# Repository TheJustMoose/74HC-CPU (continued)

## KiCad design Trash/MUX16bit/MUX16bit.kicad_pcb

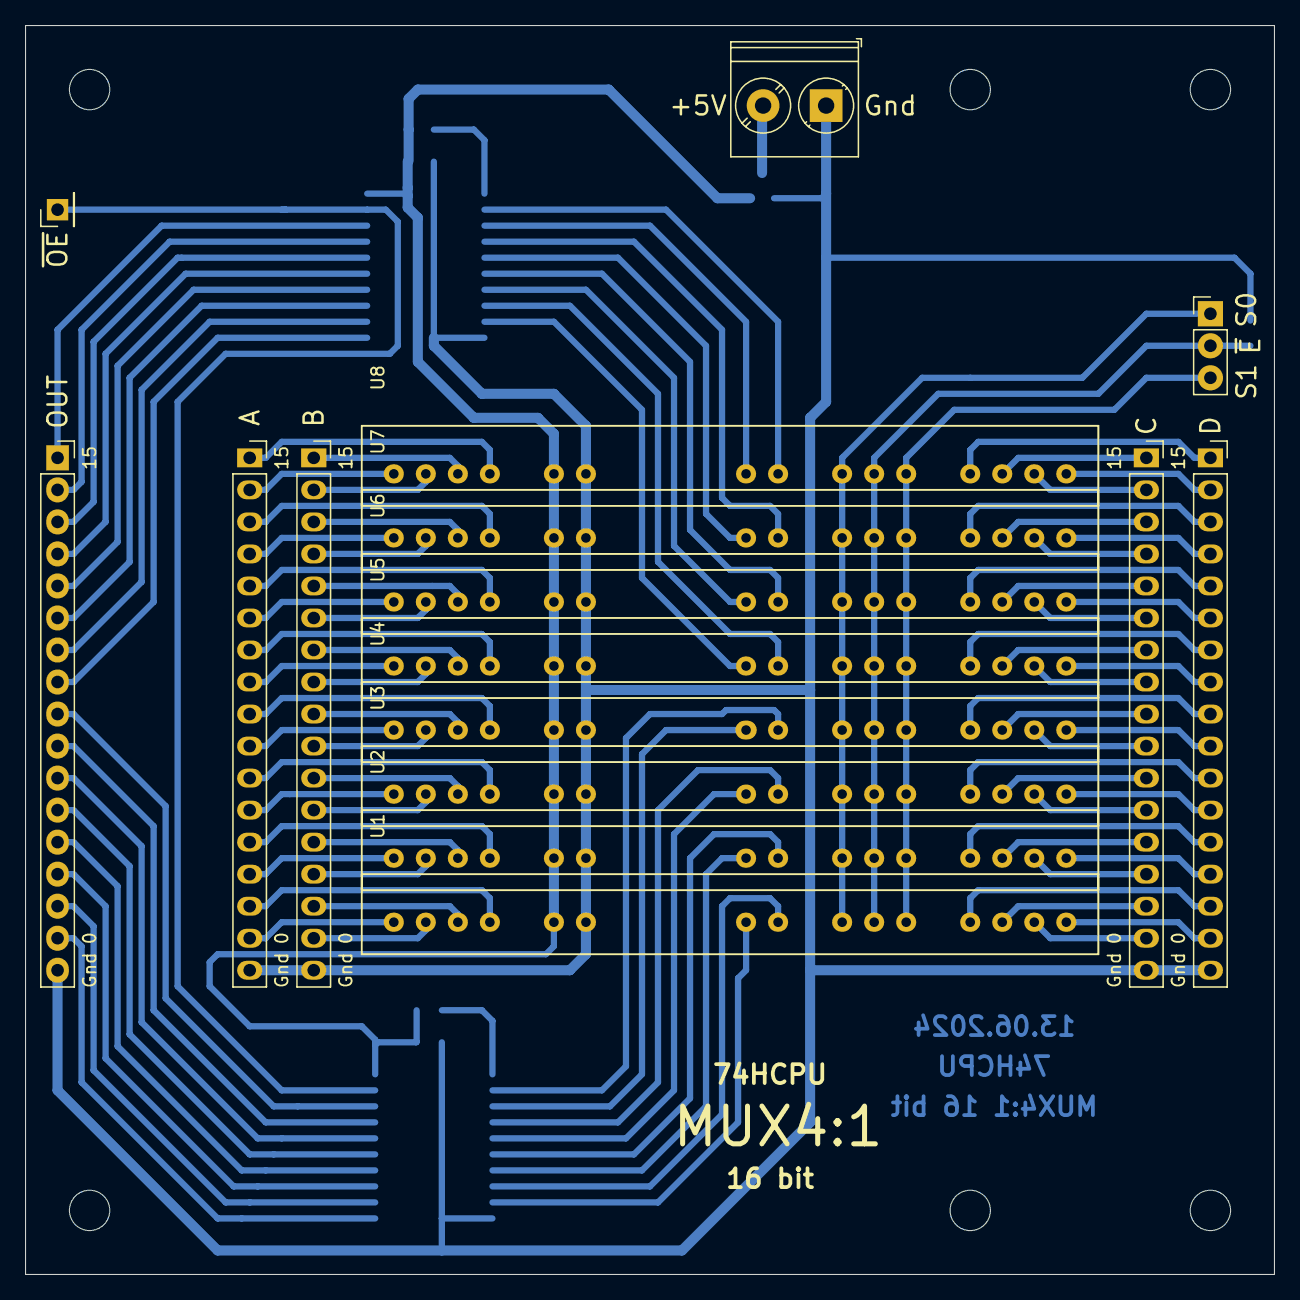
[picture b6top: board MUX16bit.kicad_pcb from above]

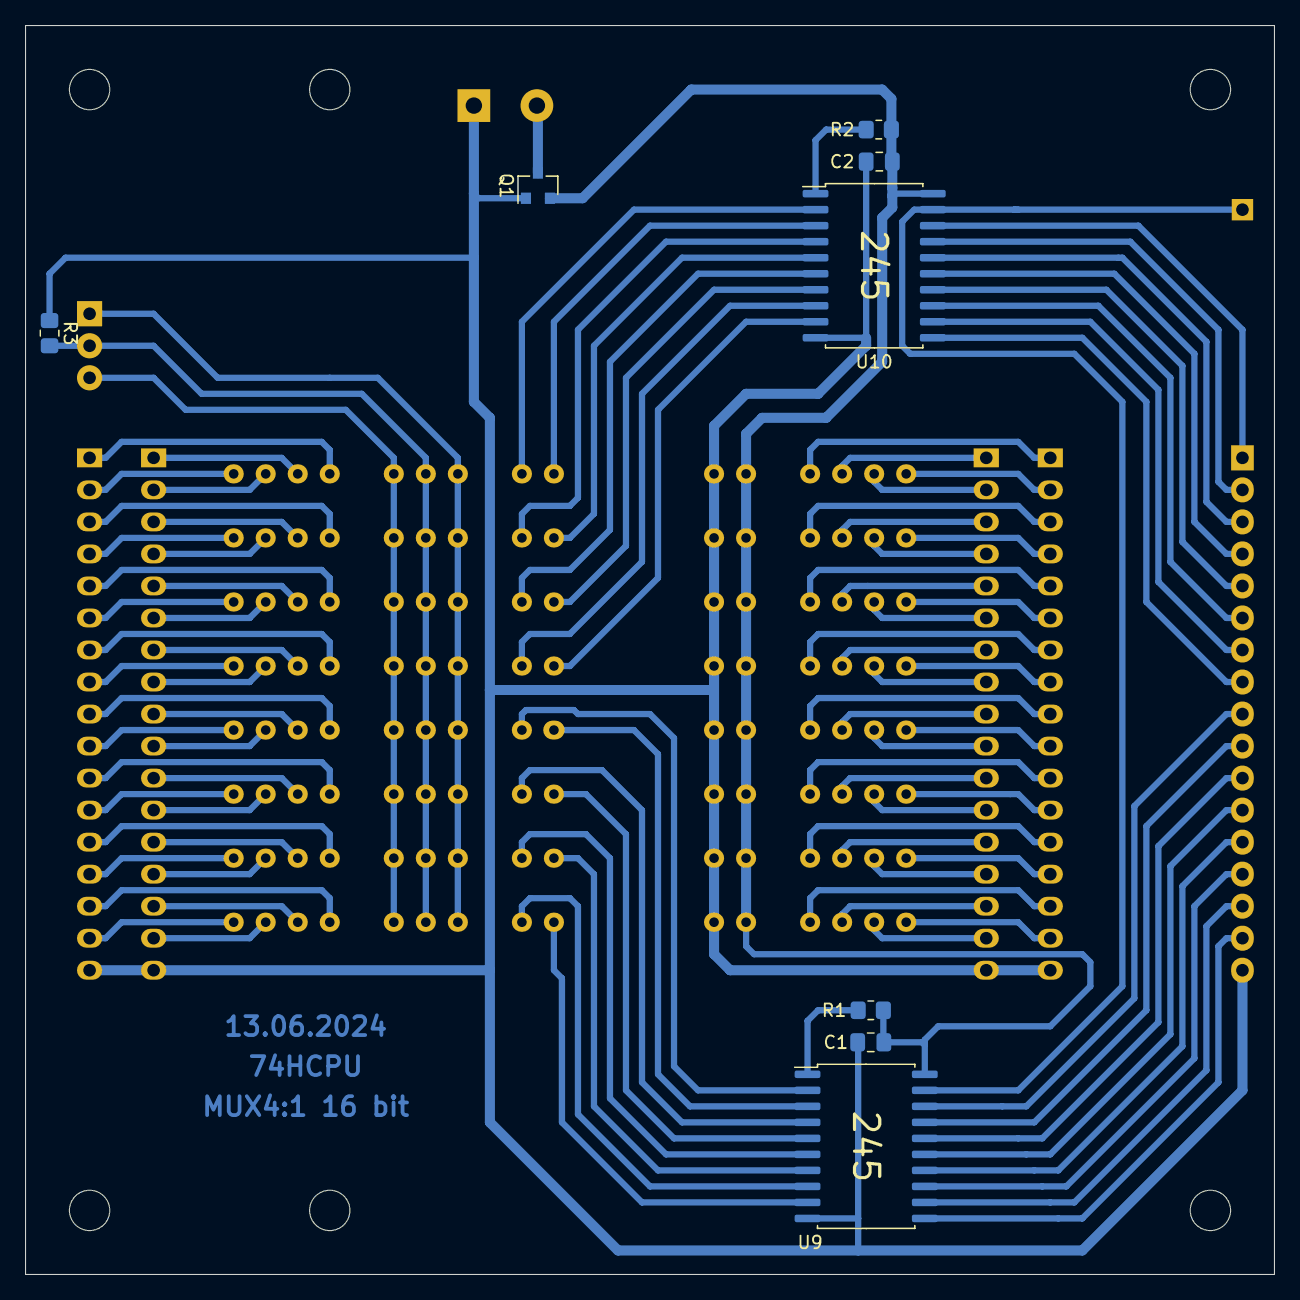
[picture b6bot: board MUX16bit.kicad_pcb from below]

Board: 2 copper layers, 99.1 x 99.1 mm, 30 parts (8 on the bottom side), 105 nets.

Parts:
C1, C2: 0.1uF; C_0805_2012Metric_Pad1.18x1.45mm_HandSolder
H1, H2, H3, H4, H5, H6: MountingHole; MountingHole_3.2mm_M3
J1, J2, J3, J4, J5: Conn_01x17_Female; PinSocket_1x17_P2.54mm_Vertical
J6: Conn_01x01_Male; PinHeader_1x01_P2.54mm_Vertical
J7: Conn_01x03_Male; PinHeader_1x03_P2.54mm_Vertical
J8: Screw_Terminal_01x02; TerminalBlock_Phoenix_PT-1,5-2-5.0-H_1x02_P5.00mm_Horizontal
Q1: IRLML5203; SOT-23
R1, R2, R3: 10k; R_0805_2012Metric_Pad1.20x1.40mm_HandSolder
U1, U2, U3, U4, U5, U6, U7, U8: MUX4; MUX1
U9, U10: 74HC245; SOIC-20W_7.5x12.8mm_P1.27mm

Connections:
/A0: J1.16, U1.1
/A1: J1.15, U1.4
/A2: J1.14, U2.1
/A3: J1.13, U2.4
/A4: J1.12, U3.1
/A5: J1.11, U3.4
/A6: J1.10, U4.1
/A7: J1.9, U4.4
/A8: J1.8, U5.1
/A9: J1.7, U5.4
/A10: J1.6, U6.1
/A11: J1.5, U6.4
/A12: J1.4, U7.1
/A13: J1.3, U7.4
/A14: J1.2, U8.1
/A15: J1.1, U8.4
/B0: J2.16, U1.2
/B1: J2.15, U1.3
/B2: J2.14, U2.2
/B3: J2.13, U2.3
/B4: J2.12, U3.2
/B5: J2.11, U3.3
/B6: J2.10, U4.2
/B7: J2.9, U4.3
/B8: J2.8, U5.2
/B9: J2.7, U5.3
/B10: J2.6, U6.2
/B11: J2.5, U6.3
/B12: J2.4, U7.2
/B13: J2.3, U7.3
/B14: J2.2, U8.2
/B15: J2.1, U8.3
/BUS0: J5.16, U9.11
/BUS1: J5.15, U9.12
/BUS2: J5.14, U9.13
/BUS3: J5.13, U9.14
/BUS4: J5.12, U9.15
/BUS5: J5.11, U9.16
/BUS6: J5.10, U9.17
/BUS7: J5.9, U9.18
/BUS8: J5.8, U10.11
/BUS9: J5.7, U10.12
/BUS10: J5.6, U10.13
/BUS11: J5.5, U10.14
/BUS12: J5.4, U10.15
/BUS13: J5.3, U10.16
/BUS14: J5.2, U10.17
/BUS15: J5.1, U10.18
/C0: J3.16, U1.14
/C1: J3.15, U1.13
/C2: J3.14, U2.14
/C3: J3.13, U2.13
/C4: J3.12, U3.14
/C5: J3.11, U3.13
/C6: J3.10, U4.14
/C7: J3.9, U4.13
/C8: J3.8, U5.14
/C9: J3.7, U5.13
/C10: J3.6, U6.14
/C11: J3.5, U6.13
/C12: J3.4, U7.14
/C13: J3.3, U7.13
/C14: J3.2, U8.14
/C15: J3.1, U8.13
/D0: J4.16, U1.15
/D1: J4.15, U1.12
/D2: J4.14, U2.15
/D3: J4.13, U2.12
/D4: J4.12, U3.15
/D5: J4.11, U3.12
/D6: J4.10, U4.15
/D7: J4.9, U4.12
/D8: J4.8, U5.15
/D9: J4.7, U5.12
/D10: J4.6, U6.15
/D11: J4.5, U6.12
/D12: J4.4, U7.15
/D13: J4.3, U7.12
/D14: J4.2, U8.15
/D15: J4.1, U8.12
/O0: U1.7, U9.9
/O1: U1.8, U9.8
/O2: U2.7, U9.7
/O3: U2.8, U9.6
/O4: U3.7, U9.5
/O5: U3.8, U9.4
/O6: U4.7, U9.3
/O7: U4.8, U9.2
/O8: U5.7, U10.9
/O9: U5.8, U10.8
/O10: U6.7, U10.7
/O11: U6.8, U10.6
/O12: U7.7, U10.5
/O13: U7.8, U10.4
/O14: U8.7, U10.3
/O15: U8.8, U10.2
/S0: J7.1, U1.9, U2.9, U3.9, U4.9, U5.9, U6.9, U7.9, U8.9
/S1: J7.3, U1.11, U2.11, U3.11, U4.11, U5.11, U6.11, U7.11, U8.11
/~E: J7.2, R3.2, U1.10, U2.10, U3.10, U4.10, U5.10, U6.10, U7.10, U8.10
/~OE: J6.1, U9.19, U10.19
GND: C1.2, C2.2, J1.17, J2.17, J3.17, J4.17, J5.17, J8.1, Q1.1, R3.1, U1.6, U2.6, U3.6, U4.6, U5.6, U6.6, U7.6, U8.6, U9.10, U10.10
unnamed: J8.2, Q1.3
unnamed: R1.1, U9.1
unnamed: R2.1, U10.1
VCC: C1.1, C2.1, Q1.2, R1.2, R2.2, U1.5, U2.5, U3.5, U4.5, U5.5, U6.5, U7.5, U8.5, U9.20, U10.20

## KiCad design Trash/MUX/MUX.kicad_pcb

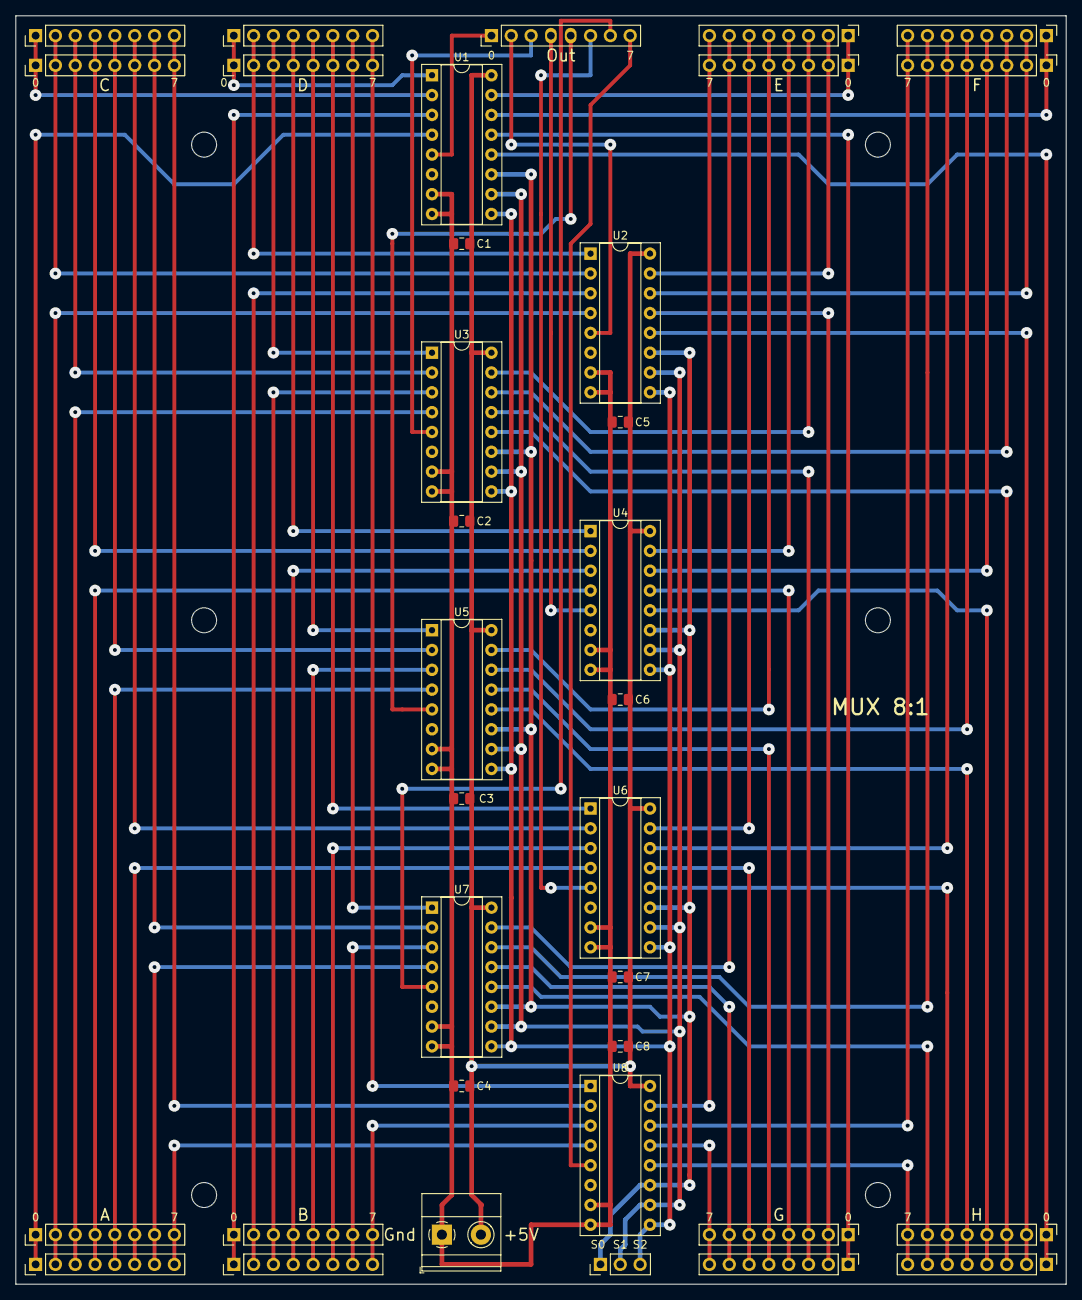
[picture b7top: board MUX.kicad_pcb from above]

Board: 2 copper layers, 134.6 x 162.6 mm, 41 parts (0 on the bottom side), 77 nets.

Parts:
C1, C2, C3, C4, C5, C6, C7, C8: 0.1uF; C_0805_2012Metric_Pad1.18x1.45mm_HandSolder
H1, H2, H3, H4, H5, H6: MountingHole; MountingHole_3.2mm_M3
J1, J2, J3, J4, J5, J6, J7, J8, J11, J12, J13, J14, J15, J16, J17, J18, J19: Conn_01x08_Male; PinHeader_1x08_P2.54mm_Vertical
J9: Screw_Terminal_01x02; TerminalBlock_Phoenix_MKDS-1,5-2_1x02_P5.00mm_Horizontal
J10: Conn_01x03_Male; PinHeader_1x03_P2.54mm_Vertical
U1, U2, U3, U4, U5, U6, U7, U8: 74LS151; DIP-16_W7.62mm_Socket

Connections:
/A0: J1.1, J12.1, U1.4
/A1: J1.2, J12.2, U2.4
/A2: J1.3, J12.3, U3.4
/A3: J1.4, J12.4, U4.4
/A4: J1.5, J12.5, U5.4
/A5: J1.6, J12.6, U6.4
/A6: J1.7, J12.7, U7.4
/A7: J1.8, J12.8, U8.4
/B0: J3.1, J14.1, U1.3
/B1: J3.2, J14.2, U2.3
/B2: J3.3, J14.3, U3.3
/B3: J3.4, J14.4, U4.3
/B4: J3.5, J14.5, U5.3
/B5: J3.6, J14.6, U6.3
/B6: J3.7, J14.7, U7.3
/B7: J3.8, J14.8, U8.3
/C0: J5.1, J16.1, U1.2
/C1: J5.2, J16.2, U2.2
/C2: J5.3, J16.3, U3.2
/C3: J5.4, J16.4, U4.2
/C4: J5.5, J16.5, U5.2
/C5: J5.6, J16.6, U6.2
/C6: J5.7, J16.7, U7.2
/C7: J5.8, J16.8, U8.2
/D0: J7.1, J18.1, U1.1
/D1: J7.2, J18.2, U2.1
/D2: J7.3, J18.3, U3.1
/D3: J7.4, J18.4, U4.1
/D4: J7.5, J18.5, U5.1
/D5: J7.6, J18.6, U6.1
/D6: J7.7, J18.7, U7.1
/D7: J7.8, J18.8, U8.1
/E0: J2.1, J13.1, U1.15
/E1: J2.2, J13.2, U2.15
/E2: J2.3, J13.3, U3.15
/E3: J2.4, J13.4, U4.15
/E4: J2.5, J13.5, U5.15
/E5: J2.6, J13.6, U6.15
/E6: J2.7, J13.7, U7.15
/E7: J2.8, J13.8, U8.15
/F0: J4.1, J15.1, U1.14
/F1: J4.2, J15.2, U2.14
/F2: J4.3, J15.3, U3.14
/F3: J4.4, J15.4, U4.14
/F4: J4.5, J15.5, U5.14
/F5: J4.6, J15.6, U6.14
/F6: J4.7, J15.7, U7.14
/F7: J4.8, J15.8, U8.14
/G0: J6.1, J17.1, U1.13
/G1: J6.2, J17.2, U2.13
/G2: J6.3, J17.3, U3.13
/G3: J6.4, J17.4, U4.13
/G4: J6.5, J17.5, U5.13
/G5: J6.6, J17.6, U6.13
/G6: J6.7, J17.7, U7.13
/G7: J6.8, J17.8, U8.13
/H0: J8.1, J19.1, U1.12
/H1: J8.2, J19.2, U2.12
/H2: J8.3, J19.3, U3.12
/H3: J8.4, J19.4, U4.12
/H4: J8.5, J19.5, U5.12
/H5: J8.6, J19.6, U6.12
/H6: J8.7, J19.7, U7.12
/H7: J8.8, J19.8, U8.12
/O0: J11.1, U1.5
/O1: J11.2, U2.5
/O2: J11.3, U3.5
/O3: J11.4, U4.5
/O4: J11.5, U5.5
/O5: J11.6, U6.5
/O6: J11.7, U7.5
/O7: J11.8, U8.5
/S0: J10.1, U1.11, U2.11, U3.11, U4.11, U5.11, U6.11, U7.11, U8.11
/S1: J10.2, U1.10, U2.10, U3.10, U4.10, U5.10, U6.10, U7.10, U8.10
/S2: J10.3, U1.9, U2.9, U3.9, U4.9, U5.9, U6.9, U7.9, U8.9
GND: C1.2, C2.2, C3.2, C4.2, C5.2, C6.2, C7.2, C8.2, J9.1, U1.7, U1.8, U2.7, U2.8, U3.7, U3.8, U4.7, U4.8, U5.7, U5.8, U6.7, U6.8, U7.7, U7.8, U8.7, U8.8
VCC: C1.1, C2.1, C3.1, C4.1, C5.1, C6.1, C7.1, C8.1, J9.2, U1.16, U2.16, U3.16, U4.16, U5.16, U6.16, U7.16, U8.16

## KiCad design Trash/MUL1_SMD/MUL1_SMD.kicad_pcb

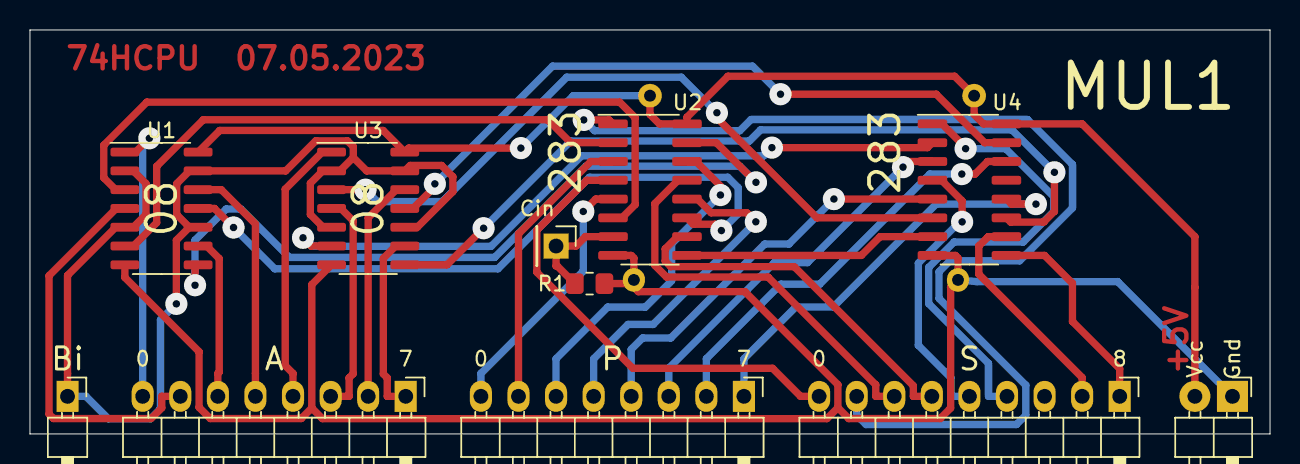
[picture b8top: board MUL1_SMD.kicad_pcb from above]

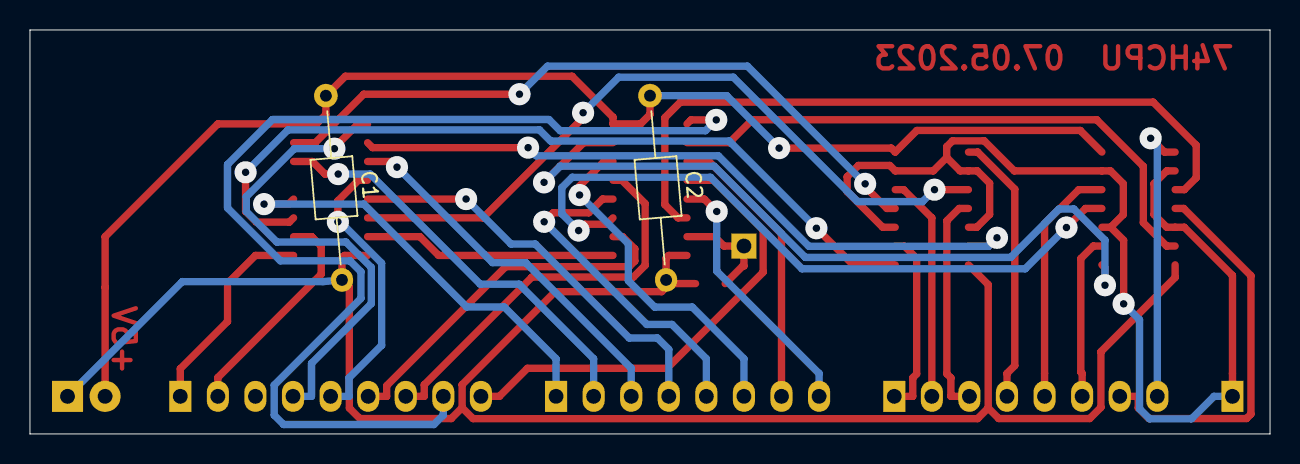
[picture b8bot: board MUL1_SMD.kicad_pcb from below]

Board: 2 copper layers, 83.8 x 27.3 mm, 13 parts (2 on the bottom side), 38 nets.

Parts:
C1, C2: 0.1uF; C_Axial_L3.8mm_D2.6mm_P12.50mm_Horizontal
J1, J3: Conn_01x08_Male; PinHeader_1x08_P2.54mm_Horizontal
J2: Conn_01x09_Male; PinHeader_1x09_P2.54mm_Horizontal
J4: Conn_01x01_Male; PinHeader_1x01_P2.54mm_Horizontal
J5: Conn_01x02_Male; PinHeader_1x02_P2.54mm_Horizontal
J6: Conn_01x01_Male; PinHeader_1x01_P2.54mm_Vertical
R1: 10k; R_0805_2012Metric_Pad1.20x1.40mm_HandSolder
U1, U3: 74LS08; SOIC-14_3.9x8.7mm_P1.27mm
U2, U4: 74LS283; SOP-16_3.9x9.9mm_P1.27mm

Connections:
/A0: J3.8, U1.1
/A1: J3.7, U1.4
/A2: J3.6, U1.9
/A3: J3.5, U1.12
/A4: J3.4, U3.1
/A5: J3.3, U3.4
/A6: J3.2, U3.12
/A7: J3.1, U3.9
/Bi: J4.1, U1.2, U1.5, U1.10, U1.13, U3.2, U3.5, U3.10, U3.13
/P0: J1.8, U2.5
/P1: J1.7, U2.3
/P2: J1.6, U2.14
/P3: J1.5, U2.12
/P4: J1.4, U4.5
/P5: J1.3, U4.3
/P6: J1.2, U4.14
/P7: J1.1, U4.12
/S0: J2.9, U2.4
/S1: J2.8, U2.1
/S2: J2.7, U2.13
/S3: J2.6, U2.10
/S4: J2.5, U4.4
/S5: J2.4, U4.1
/S6: J2.3, U4.13
/S7: J2.2, U4.10
/S8: J2.1, U4.9
GND: C1.2, C2.2, J5.1, R1.1, U1.7, U2.8, U3.7, U4.8
unnamed: J6.1, R1.2, U2.7
unnamed: U1.3, U2.6
unnamed: U1.6, U2.2
unnamed: U1.8, U2.15
unnamed: U1.11, U2.11
unnamed: U2.9, U4.7
unnamed: U3.3, U4.6
unnamed: U3.6, U4.2
unnamed: U3.8, U4.11
unnamed: U3.11, U4.15
VCC: C1.1, C2.1, J5.2, U1.14, U2.16, U3.14, U4.16

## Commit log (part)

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2024-02-29 ASM in work: it works!
2024-02-29 ASM in work: add line number to output
2024-02-29 ASM in work: try to process strings
2024-03-01 ASM in work: lost hex
2024-03-01 ASM in work: collect string addresses into table
2024-03-01 ASM in work: try to process .def directive
2024-03-01 ASM in work: .def with param
2024-03-01 ASM in work: try to apply .def directive
2024-03-01 ASM in work: add message about macro
2024-03-07 ASM in work: fix PTR enum values, fix strings
2024-03-07 ASM in work: try to process post increment/decrement
2024-03-07 ASM in work: try to process strings addresses
2024-03-08 ASM in work: polishing
2024-03-08 ASM in work: add new register names
2024-03-08 ASM in work: add HI/LO function to split addresses
2024-03-08 ASM in work: add LPMW operation
2024-03-08 fix description
2024-03-08 ASM in work: try to implement TOGL operation
2024-03-09 ASM in work: fix bug, add build script
2024-03-09 ASM in work: split asm.cc to modules
2024-03-10 ASM in work: try to add submodule with doctest
2024-03-10 ASM in work: reorder code in files
2024-03-10 ASM in work: add empty unit test
2024-03-10 ASM in work: add tests for line strip
2024-03-10 ASM in work: polishing tests
2024-03-10 ASM in work: we need more tests!!
2024-03-10 ASM in work: preprocessor in work
2024-03-10 ideas
2024-03-11 ASM in work: test file
2024-03-11 ASM in work: fix tests
2024-03-11 ASM in work: we need more tests
2024-03-11 ASM in work: simple define was implemented
2024-03-11 ASM in work: polishing preprocessor
2024-03-11 ASM in work: adding defines with params into preprocessor
2024-03-11 ASM in work: preprocessor in work, temp commit
2024-03-12 ALU pdf
2024-03-12 ALU: some lost file
2024-03-12 LED8 gerber
2024-03-12 Try to create SMD version of multiplier
2024-03-12 gerbers for MUX8x1 reverted
2024-03-12 One more proto board (3-2-3)
2024-03-12 Pdf for reg board
2024-03-12 Regs v3 pcb gerbers
2024-03-12 Gerbers for Toggler pcb
2024-03-12 Some Reg with bad order of bits
2024-03-12 CPU v2 structure
2024-03-12 ASM in work: preprocessor .def works
2024-03-12 ASM in work: remove logs
2024-03-12 ASM in work: fix crash in preprocessor, rename some methods
2024-03-12 ASM in work: now preprocessor live in separate unit
2024-03-12 ASM in work
2024-03-12 ASM in work: example fixes
2024-03-13 ASM in work: try to preprocess labels
2024-03-13 ASM in work: cmd arg to show preprocessed asm
2024-03-13 ASM in work: other way to parse commands
2024-03-13 ASM in work: remove comments, remove unused var 'tail'
2024-03-13 ASM in work: remove unused code
2024-03-14 ASM in work: fix getting ptr offset
2024-03-14 ASM in work: fix error reporting for string addresses
2024-03-14 ASM in work: fix description & example
2024-03-19 New reg in work
2024-03-20 Register with LEDs & reset is ready
2024-03-20 Wrong folder. Just rename.
2024-03-21 Polishing Reg 273
2024-03-21 Add gerbers for Reg 273
2024-03-21 Add gerbers for Dual Port Reg
2024-03-21 Add gerbers, fix PTH for Regs v4
2024-03-22 playing with Python
2024-03-23 just rename folder
2024-03-23 uC in work: try to implement Dragon Book compiler
2024-03-24 uC in work: fix headers
2024-03-24 uC in work: moving code from Java to C++
2024-03-24 uC in work
2024-03-24 uC in work: log file is not required
2024-03-24 uC in work: add git ignore
2024-03-25 uC in work: try to fix lexeme owning
2024-03-28 uC in work: fix some files, add unit test template
2024-03-28 uC in work: fix build.bat
2024-03-28 uC in work: try to test Lexer
2024-03-29 uC in work: bugfixing
2024-03-29 uC in work: try to fix objects owning
2024-03-29 uC in work: try to remove some files
2024-03-30 uC in work: try to replace raw ptr to shared_ptr
2024-03-30 uC in work: Type class was moved into word.h
2024-03-30 uC in work: is not required
2024-03-30 uC in work: can use inherited type
2024-03-30 uC in work: move functions into separate unit
2024-03-30 uC in work: moving Word class
2024-03-30 uC in work: remove .exe from repo
2024-03-30 uC in work: moving Word class, fix .gitignore
2024-03-30 uC in work: move impl to header
2024-03-30 uC in work: we need more tests!!
2024-03-30 uC in work: try to use local objects
2024-03-30 uC in work: fix ID recognizing
2024-03-30 uC in work: try to make parser
2024-04-03 uC in work: making parser
2024-04-03 uC in work: in work
2024-04-05 uC in work: try to check Env class
2024-04-05 uC in work: fix build ;))
2024-04-06 uC in work: try to use raw pointers instead of shared_ptr
2024-04-26 Add description about objects owning.
2024-04-26 Playing with tkinter
2024-04-26 polishing instruction set
2024-04-27 new CPU structure
2024-04-28 polishing CPU structure
2024-04-28 uC in work: add Type methods
2024-04-28 todos
2024-05-12 rename
2024-05-12 rename img
2024-05-14 fix CPU structure diagram
2024-05-14 CPU tacts
2024-05-14 Add CPU tacts to README.md
2024-05-14 polishing
2024-05-16 Polishing Ports & LCD
2024-05-16 Polishing Regs-v4
2024-05-18 Try to add AddrCnt to MUX4:1
2024-05-24 16 bit stack, 1 level ;)
2024-05-26 Polishing Stack16
2024-06-12 MUX4:1, 1bit narrow version
2024-06-13 MUX4:1, 1bit - set minimum size == 12.7mm
2024-06-13 Polishing MUX16bit
2024-06-15 Address counter in work
2024-06-16 Address counter in work. Set power pins in center of the MUX PCB.
2024-06-16 Address counter is almost ready ;)
2024-06-16 Fix MUX1 (4:1, 1 bit) sizes. Set 10mm between power and other pins.
2024-06-16 Fix MUX1 gerbers.
2024-06-18 Polishing Address counter
2024-06-20 Address counter. Add gerbers. Remove stack counter.
2024-06-20 Regs-v4, update gerbers
2024-06-24 Try to draw power bus ;)
2024-07-20 Set "standard" size for RAM (99.06 x 99.06)
2024-07-20 Update gerbers & remove pdfs
2024-07-20 Move sockets
2024-07-20 Power bus is ready
2024-07-21 Old MUX8:1 - fix silk
2024-07-21 Add gerber
2024-07-21 Add gerbers for stack16
2024-07-21 ALU is almost ready
2024-07-21 Add gerbers & pdf
2024-07-22 RAM - move data socket to left side
2024-07-22 Polishing RAM
2024-07-22 74HCPU PCB layers
2024-07-22 Try to convert html to md
2024-07-22 Playing with MD
2024-07-22 Try to remove borders
2024-07-22 Convert html to md
2024-07-22 Fix img sizes
2024-07-22 bugfixing md
2024-07-22 Try to add link
2024-07-23 Polishing Power Bus
2024-07-23 ToDos & Panels in work
2024-07-23 MUL 8x8 in work
2024-07-23 Some changes in ALU
2024-07-23 .pyc files are not required
2024-07-23 Polishing ALU & update pdfs & gerbers
2024-07-24 Update ALU picture
2024-07-24 Invertor doesn't have output buffer so I removed output pinheaders
2024-07-24 Polishing ALU
2024-07-24 Polishing ALU. Update gerbers (not pdf)
2024-07-25 Polishing layers
2024-07-25 Try to add spaces
2024-07-25 Try to use html
2024-07-25 Try to use 1px image
2024-07-26 Update ALU image
2024-07-26 RAM v1.1, move sockets to left
2024-07-26 Update SRAM img
2024-07-26 Update ALU img
2024-07-26 Ports is ready
2024-07-26 Update Ports img
2024-08-04 MUL cmd in work
2024-08-05 Multiplier is ready
2024-08-05 Update multiplier img
2024-08-12 Polishing Multiplier
2024-08-13 update multiplier image
2024-08-13 ROM in work Try to rotate ROM socket
2024-08-14 Polishing ROM Add gerber
2024-08-14 Bug fix ALU Update gerber
2024-08-14 Update MUL Add gerbers
2024-08-14 Polishing RAM Update gerbers
2024-08-14 Update gerbers for PwrBus
2024-08-14 Update gerbers for Ports
2024-08-16 Move some pcbs to subfolders
2024-08-16 Move files to trash
2024-08-16 Update gerbers
2024-08-16 Move MUX16bit to Trash
2024-08-16 Combine some PCBs to groups
2024-08-16 Lost file
2024-08-16 Rename some dirs
2024-08-16 Move Toggle to Ports
2024-08-16 Ports v1.4 Polishing, move power connector to left
2024-08-16 Update ALU & Ports screenshots
2024-08-16 Update ROM screenshot
2024-08-17 List of wires of modules (in work)
2024-08-17 Add descriptions for almost all pcb pins!
2024-09-15 1251 -> utf-8
2024-10-26 MUX8:1 remake
2024-10-26 Playing with keyboard
2024-10-31 Fix CPU structure
2024-11-13 Kbd in work
2024-11-29 Parser in work. Continue converting Java -> Cpp
2024-12-12 Playing with Regs PCB v5
2024-12-15 Regs v5 in work
2024-12-15 MUX 8:1 r2 in work
2024-12-18 Try to create emulator of 74hcpu
2024-12-25 74hcpu emulator initial commit
2024-12-27 74hcpu emulator in work
2024-12-27 Add some Instructions
2024-12-28 Add consts
2024-12-28 Try to implement ADD
2024-12-28 We need more classes
2024-12-29 Add ROM reading from file
2024-12-29 Emul in work
2024-12-30 Emul bugfixing
2024-12-30 Add doctest as submodule
2024-12-30 Extract consts into header. Add tests.
2024-12-30 Try to ignore doctest
2024-12-30 Move method to proper class
2024-12-31 union != struct *ROFL*
2024-12-31 Remove debug code
2025-01-01 We need more operations
2025-01-05 Polishing RegCntDualPort
2025-01-06 Move PCBs into subfolder hard
2025-01-06 Polishing RegCntLedDualPort
2025-01-07 RegCntLedDualPort is ready
2025-01-28 Regs v5 is ready
2025-01-29 Regs v5: add gerbers
2025-01-30 Polishing Dual Reg Cnt
2025-01-30 Polishing Reg273
2025-01-30 Reg 273: update gerbers
2025-01-30 Dual RegCnt: update gerbers
2025-01-30 Regs v5: update gerbers
2025-04-13 MUX8:1 in work
2025-04-13 MUX8:1 in [re]work
2025-05-14 mux 8:1 in work
2025-06-01 Working on Regs v6
2025-06-01 Regs v6 in work
2025-06-12 Regs v6 pcb is almost ready
2025-06-12 Regs v6 pcb is ready!
2025-06-25 MUX8:1, 1 bit
2025-06-25 Polishing MUX8:1
2025-07-20 Compiler in work
2025-07-29 Hooray! Unit tests build ok!
2025-08-13 Polishing Regs v6
2025-09-21 Debugging, bugfixing, etc...
2025-10-04 Add flag names
2025-10-04 Remove some old files
2025-10-06 The simplest version of emul
2025-10-06 Add test commands
2025-10-11 Add I/O ports table
2025-10-15 Fix port names in asm
2025-10-15 More unit tests
2025-10-19 Bugfixing
2025-10-20 Gerber for 1 bit MUX 8:1
2025-10-20 Just rename files
2025-10-20 Assembler in work
2025-10-24 Not used
2025-10-24 Extract string utils
2025-10-24 Extract class for errors
2025-10-24 New tests. Broken ;)
2025-10-26 We need more tests...
2025-10-27 Move trim func to str_util
2025-10-27 Just rename
2025-10-27 Convert build system to cmake
2025-10-29 Uno cmd test (broken!)
2025-10-29 More uno cmd tests!
2025-10-31 Move func to proper place
2025-10-31 I don't know how to use C in MOV!
2025-10-31 Replace UINT to uint16_t
2025-10-31 Test for MOV cmd
2025-11-02 Test for memory operations
2025-11-02 Test LPM operations
2025-11-02 Try to fix description
2025-11-02 Change POINTER register mask from F to 3 (3 to 2 bits) and add unit test
2025-11-02 Test + description
2025-11-02 Unit test for IN + small check for TAB
2025-11-03 Test OUT cmd
2025-11-03 Try to test branches
2025-11-03 Fix crash
2025-11-03 Fix some branch codes
2025-11-03 Tests for branches is ready
2025-11-04 Unit tests for jump distances
2025-11-04 Split the tests into two parts
2025-11-04 Move ErrorCollector to separate unit
2025-11-04 Working on error list
2025-11-04 Try to add error reporting
2025-11-04 Polishing error reporting
2025-11-04 Fix debug print
2025-11-06 Split tests to more files
2025-11-07 Writing machine code to file
2025-11-07 Fix dumb error ;)
2025-11-07 Add string out to binary file
2025-11-07 Fix .org error. Rename unit test
2025-11-07 We need more tests!!
2025-11-07 Try to test register names
2025-11-07 Replace static methods to Singleton & our class
2025-11-07 Convert pointer to reference
2025-11-07 Combine two class into one. I hope it still Singleton ;)
2025-11-07 Fix command line args processing
2025-11-08 More tests for more names
2025-11-08 Add file reading to uemul
2025-11-08 Extract function ReadHex
2025-11-09 Disasm opcode in uemul
2025-11-09 One little step to disasm
2025-11-10 Continue disasm. Add classes for operations
2025-11-10 Emul im work
2025-11-10 Convert switch (op) to if-s
2025-11-10 Reorder if-s
2025-11-10 Try to fix memory op-s
2025-11-11 Try to fix IP calculating
2025-11-12 Oops. Lost ip++
2025-11-12 Try to minimize code
2025-11-12 Fix jump cops
2025-11-12 Fix calls return address
2025-11-13 Split string
